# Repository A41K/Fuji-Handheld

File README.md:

## Fuji Handheld
- A small pocket sized gameboy ask console with controls, 2.0' TFT screen, 2 pre-made games and a usb port

## PCB

## Schematic

## Software

The software can be found in the /Firmware file

The pre programmed two games (pong, snake) can be found in the /games folder

everything can be changed around according to the MCU.

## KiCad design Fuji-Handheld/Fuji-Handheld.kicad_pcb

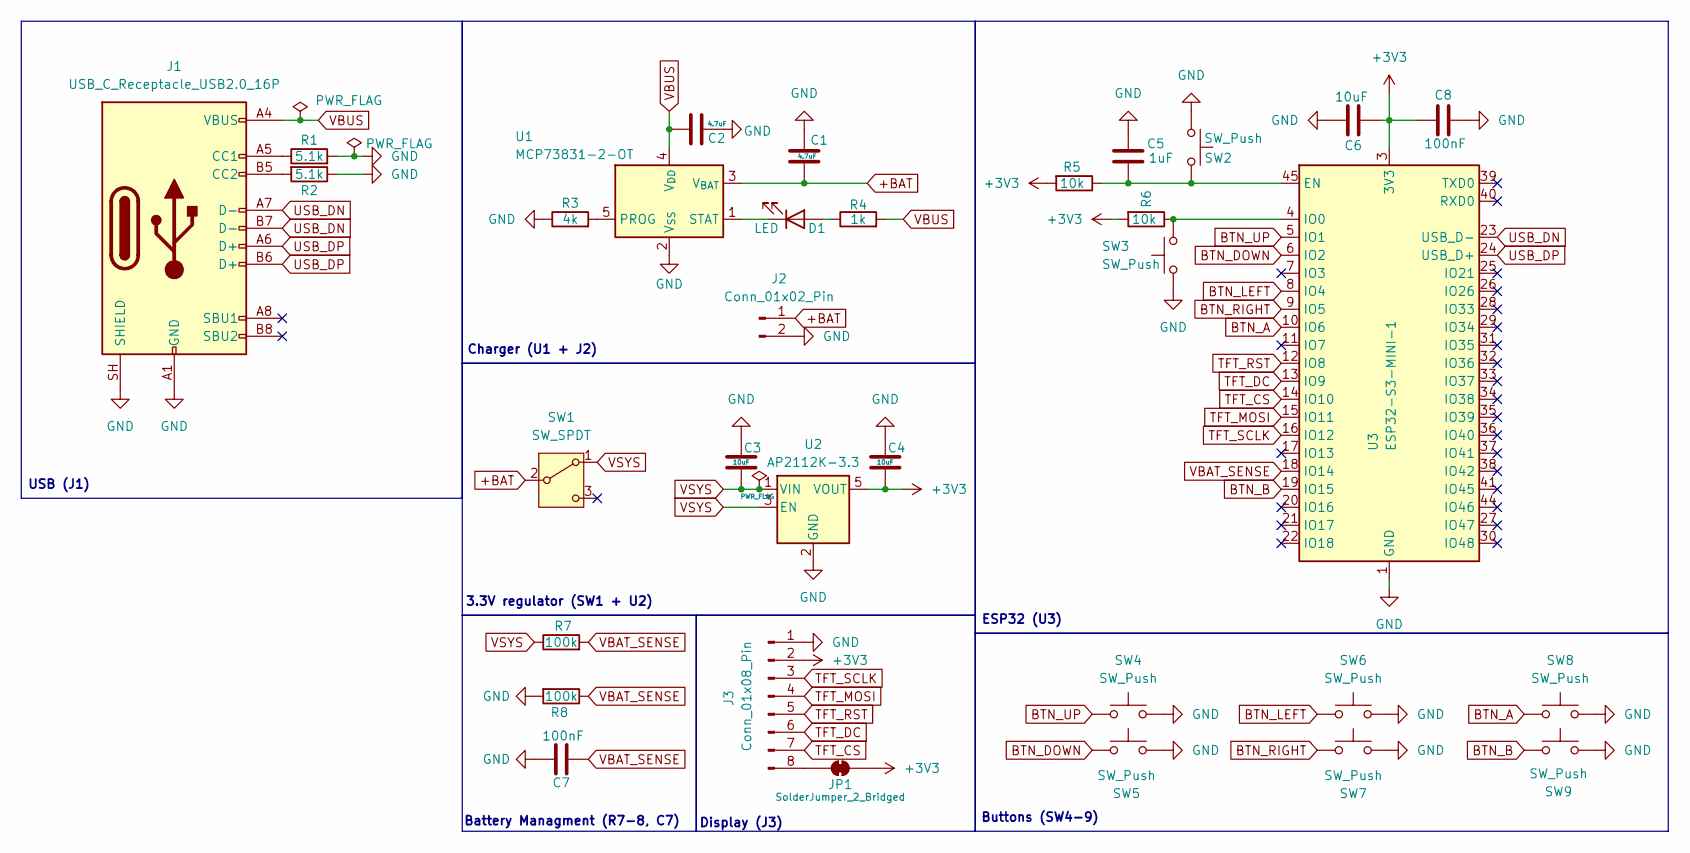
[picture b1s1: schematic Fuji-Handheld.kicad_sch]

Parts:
C1, C2: 4.7uF; C_0805_2012Metric_Pad1.18x1.45mm_HandSolder
C3, C4, C6: 10uF; C_0805_2012Metric_Pad1.18x1.45mm_HandSolder
C5: 1uF; C_0805_2012Metric_Pad1.18x1.45mm_HandSolder
C7, C8: 100nF; C_0805_2012Metric_Pad1.18x1.45mm_HandSolder
D1: LED; LED_D3.0mm
J1: USB_C_Receptacle_USB2.0_16P; USB_C_Receptacle_HRO_TYPE-C-31-M-12
J2: Conn_01x02_Pin; JST_PH_B2B-PH-K_1x02_P2.00mm_Vertical
J3: Conn_01x08_Pin; PinHeader_1x08_P2.54mm_Vertical
JP1: SolderJumper_2_Bridged; SolderJumper-2_P1.3mm_Bridged_RoundedPad1.0x1.5mm
R1, R2: 5.1k; R_0805_2012Metric_Pad1.20x1.40mm_HandSolder
R3: 4k; R_0805_2012Metric_Pad1.20x1.40mm_HandSolder
R4: 1k; R_0805_2012Metric_Pad1.20x1.40mm_HandSolder
R5, R6: 10k; R_0805_2012Metric_Pad1.20x1.40mm_HandSolder
R7, R8: 100k; R_0805_2012Metric_Pad1.20x1.40mm_HandSolder
SW1: SW_SPDT; SW_SPDT_PCM12
SW2, SW3: SW_Push; SW_SPST_PTS810
SW4, SW5, SW6, SW7, SW8, SW9: SW_Push; SW_PUSH_6mm_H4.3mm
U1: MCP73831-2-OT; SOT-23-5
U2: AP2112K-3.3; SOT-23-5
U3: ESP32-S3-MINI-1; ESP32-S2-MINI-1

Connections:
+3V3: C4.2, C6.2, C8.2, J3.2, JP1.2 (B), R5.2, R6.2, U2.5 (VOUT), U3.3 (3V3)
+BAT: C1.2, J2.1, SW1.2 (B), U1.3 (V_{BAT})
BTN_A: SW8.1, U3.10 (IO6)
BTN_B: SW9.1, U3.19 (IO15)
BTN_DOWN: SW5.1, U3.6 (IO2)
BTN_LEFT: SW6.1, U3.8 (IO4)
BTN_RIGHT: SW7.1, U3.9 (IO5)
BTN_UP: SW4.1, U3.5 (IO1)
GND: C1.1, C2.1, C3.1, C4.1, C5.1, C6.1, C7.1, C8.1, J1.A1 (GND), J1.A12 (GND), J1.B1 (GND), J1.B12 (GND), J1.SH (SHIELD), J2.2, J3.1, R1.2, R2.1, R3.1, R8.2, SW2.1, SW3.1, SW4.2, SW5.2, SW6.2, SW7.2, SW8.2, SW9.2, U1.2 (V_{SS}), U2.2 (GND), U3.1 (GND), U3.2 (GND), U3.42 (GND), U3.43 (GND), U3.46 (GND), U3.47 (GND), U3.48 (GND), U3.49 (GND), U3.50 (GND), U3.51 (GND), U3.52 (GND), U3.53 (GND), U3.54 (GND), U3.55 (GND), U3.56 (GND), U3.57 (GND), U3.58 (GND), U3.59 (GND), U3.60 (GND), U3.61 (GND), U3.62 (GND), U3.63 (GND), U3.64 (GND), U3.65 (GND)
unnamed: D1.2 (A), R4.1
unnamed: D1.1 (K), U1.1 (STAT)
unnamed: J1.A5 (CC1), R1.1
unnamed: J1.B5 (CC2), R2.2
unnamed: J3.8, JP1.1 (A)
unnamed: R3.2, U1.5 (PROG)
unnamed: C5.2, R5.1, SW2.2, U3.45 (EN)
unnamed: R6.1, SW3.2, U3.4 (IO0)
TFT_CS: J3.7, U3.14 (IO10)
TFT_DC: J3.6, U3.13 (IO9)
TFT_MOSI: J3.4, U3.15 (IO11)
TFT_RST: J3.5, U3.12 (IO8)
TFT_SCLK: J3.3, U3.16 (IO12)
USB_DN: J1.A7 (D-), J1.B7 (D-), U3.23 (USB_D-)
USB_DP: J1.A6 (D+), J1.B6 (D+), U3.24 (USB_D+)
VBAT_SENSE: C7.2, R7.2, R8.1, U3.18 (IO14)
VBUS: C2.2, J1.A4 (VBUS), J1.A9 (VBUS), J1.B4 (VBUS), J1.B9 (VBUS), R4.2, U1.4 (V_{DD})
VSYS: C3.2, R7.1, SW1.1 (A), U2.1 (VIN), U2.3 (EN)

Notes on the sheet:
Battery Managment (R7-8, C7)
Charger (U1 + J2)
Buttons (SW4-9)
Display (J3)
USB (J1)
3.3V regulator (SW1 + U2)
ESP32 (U3)

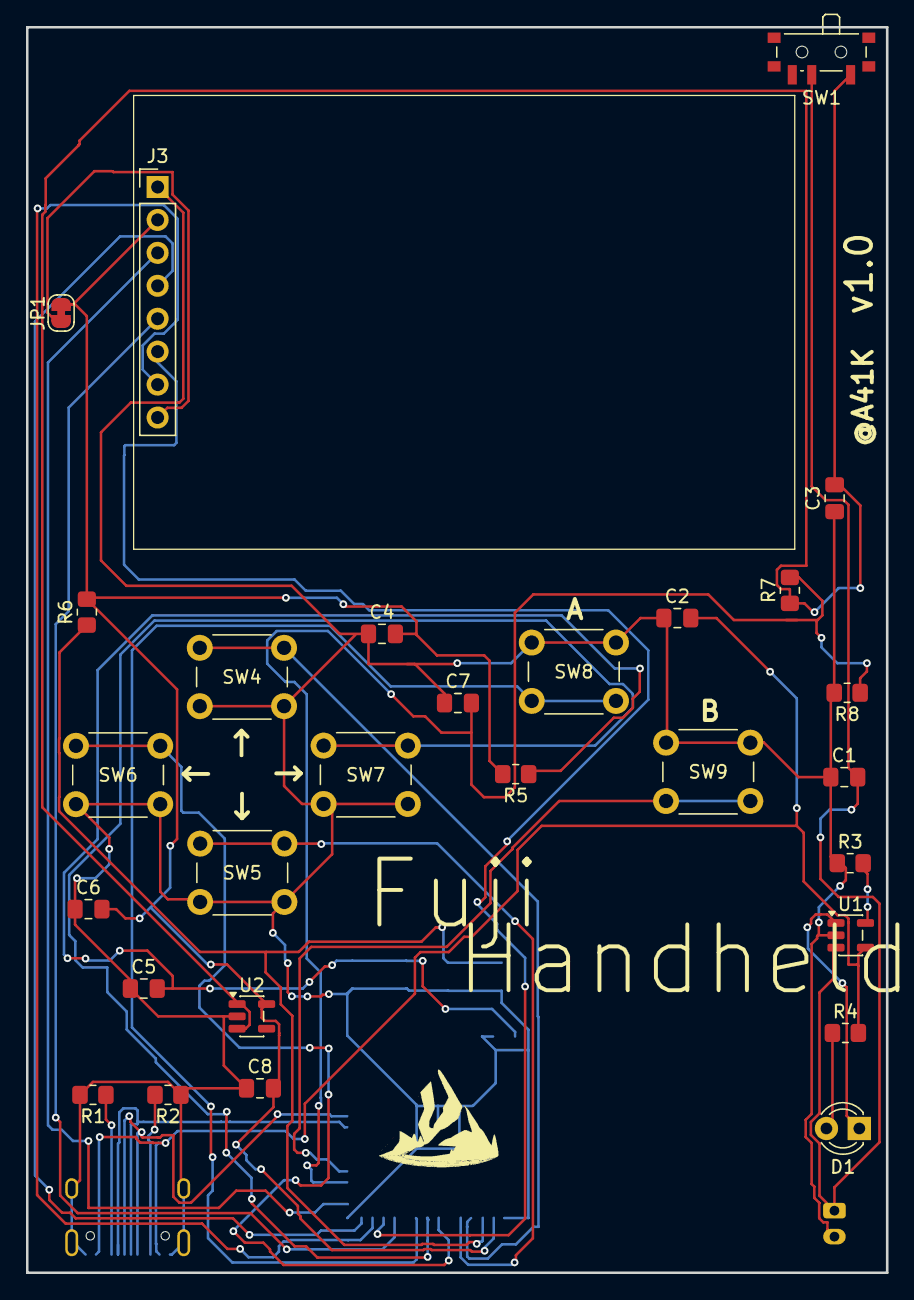
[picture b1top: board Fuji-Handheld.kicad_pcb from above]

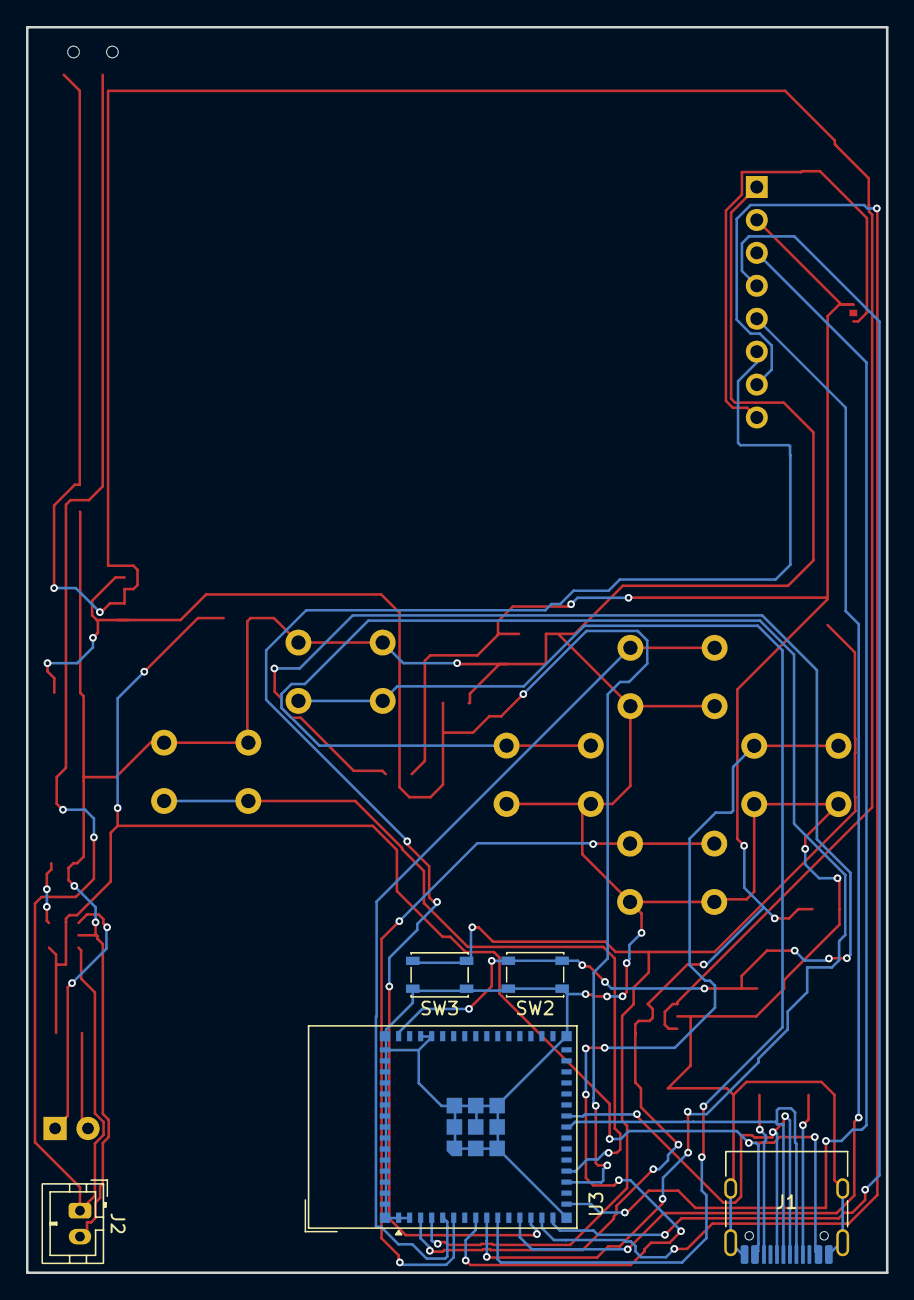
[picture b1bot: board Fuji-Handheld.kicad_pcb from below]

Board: 2 copper layers, 66.3 x 96.1 mm, 33 parts (5 on the bottom side), 27 nets.

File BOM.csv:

Item,Qty,Supplier,Cost/item,Total Cost,link
4.7uF,2,,$0.00,$0.00,
10uF,3,,$0.00,$0.00,
1uF,1,,$0.00,$0.00,
100nF,2,,$0.00,$0.00,
LED,1,,$0.00,$0.00,
USB_C_Receptacle_USB2.0_16P,1,,$0.00,$0.00,
Conn_01x02_Pin,1,,$0.00,$0.00,
Conn_01x08_Pin,1,,$0.00,$0.00,
5.1k,2,,$0.00,$0.00,
4k,1,,$0.00,$0.00,
1k,1,,$0.00,$0.00,
10k,2,,$0.00,$0.00,
100k,2,,$0.00,$0.00,
SW_SPDT,1,,$0.00,$0.00,
SW_Push,2,,$0.00,$0.00,
SW_Push,6,,$0.00,$0.00,
MCP73831-2-OT,1,,$0.00,$0.00,
AP2112K-3.3,1,,$0.00,$0.00,
ESP32-S3-MINI-1,1,,$0.00,$0.00,
Estimated total shipping,1,,,$0.00,
